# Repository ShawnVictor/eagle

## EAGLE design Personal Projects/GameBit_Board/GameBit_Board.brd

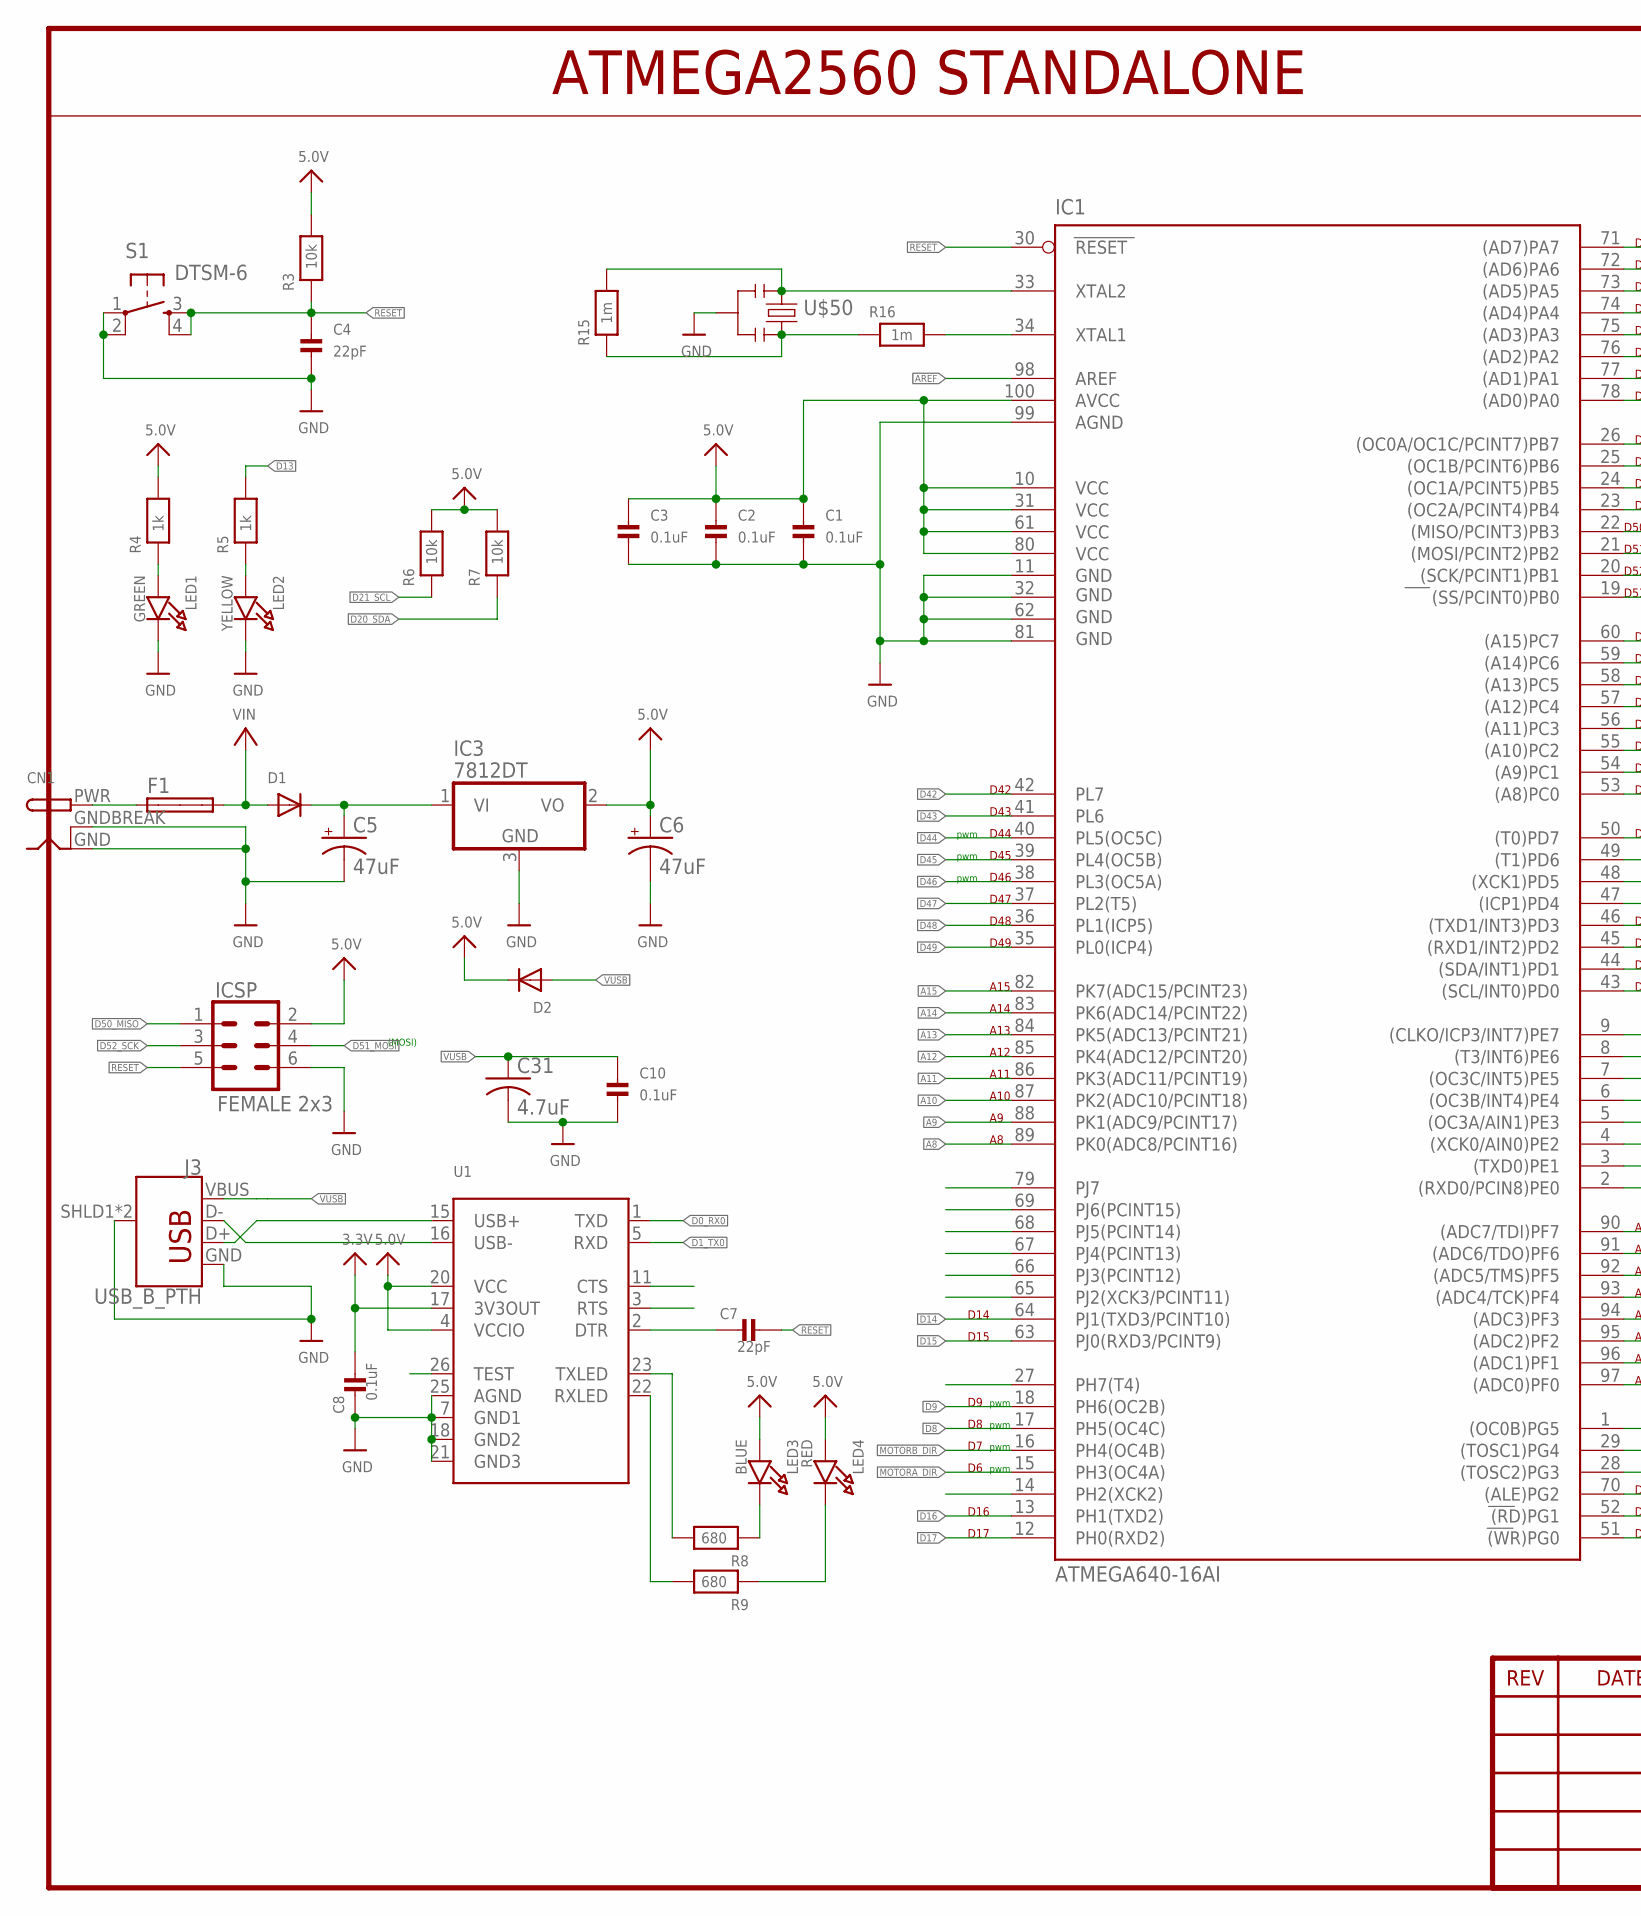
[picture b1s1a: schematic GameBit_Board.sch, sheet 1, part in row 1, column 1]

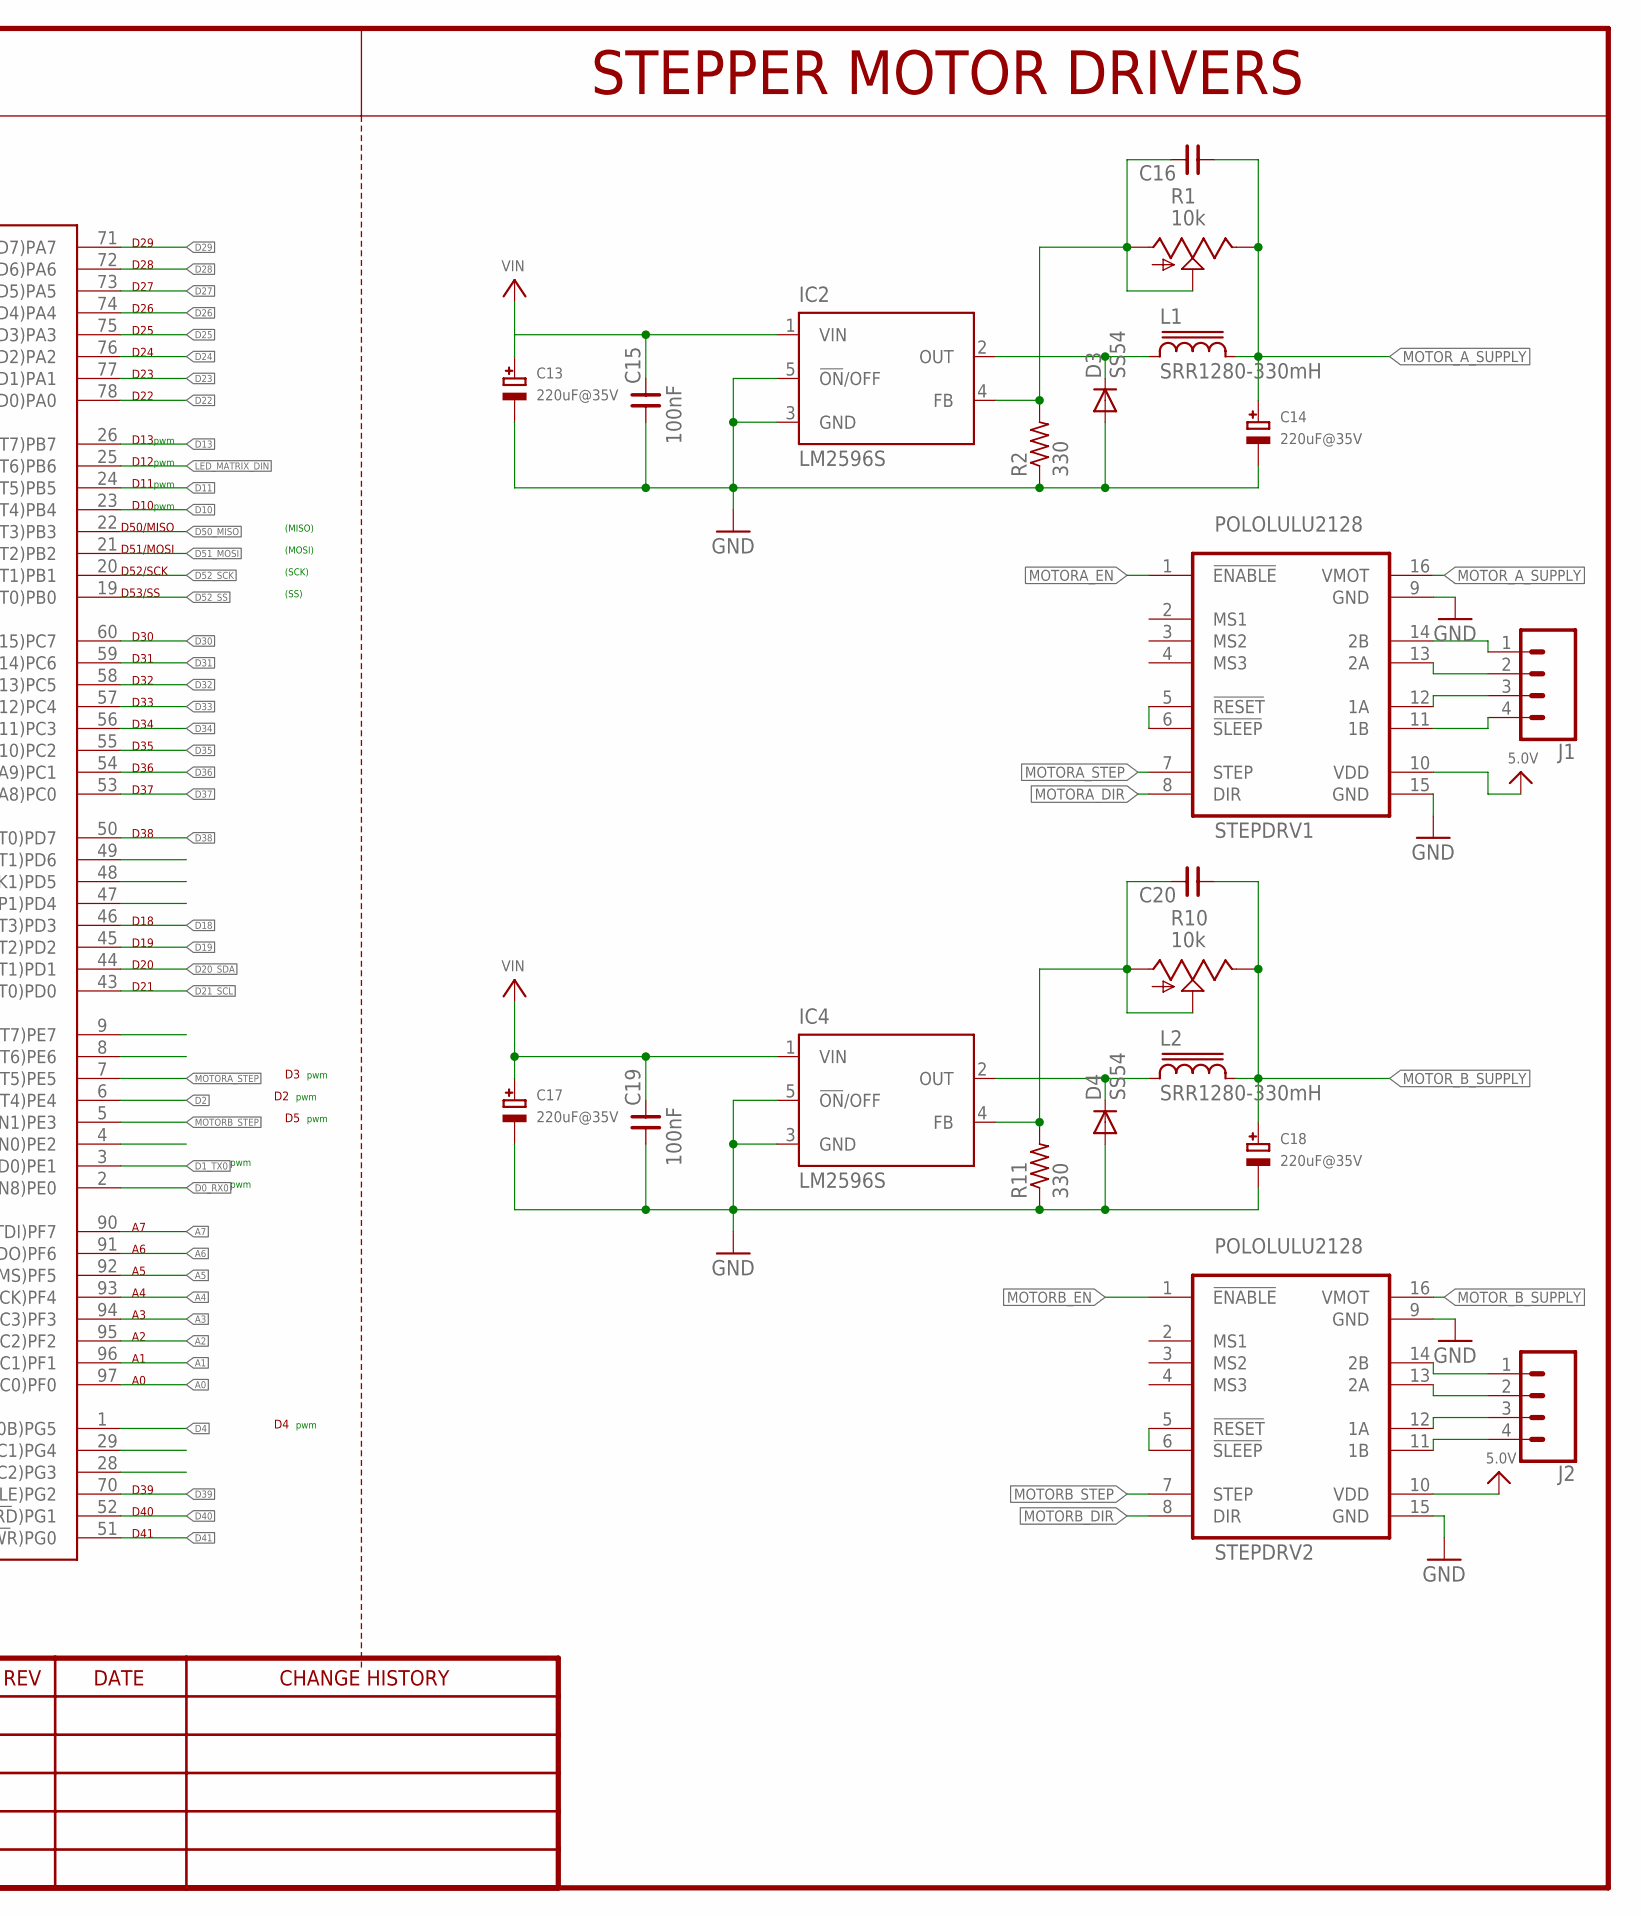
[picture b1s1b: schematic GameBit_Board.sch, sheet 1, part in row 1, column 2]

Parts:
C1, C2, C3, C8, C10: 0.1uF; 0603
C4, C7: 22pF; 0603
C5, C6: 47uF; PANASONIC_D
C13, C14, C17, C18: 220uF@35V; PANASONIC_D
C15, C19: 100nF; 0603
C16, C20: CNP-0603; 0603
C31: 4.7uF; C0805
CN1: DCBARRELPTH; DCJACK_2MM_PTH
D1, D2: DIODESOD-123; SOD-123
D3, D4: SS54; DO214AB
F1: SHK20L
IC1: ATMEGA640-16AI; TQFP100
IC2, IC4: LM2596S; TO263-5
IC3: 7812DT; TO252
ICSP: FEMALE 2x3; 2X3
J1, J2: CONN_04JST-PTH-VERT; JST-4-PTH-VERT
J3: USB_B_PTH; USB-B-PTH
L1, L2: SRR1280-330mH; SRR1280
LED1: GREEN; CHIPLED_0603
LED2: YELLOW; CHIPLED_0603
LED3: BLUE; CHIPLED_0603
LED4: RED; CHIPLED_0603
R1, R10: 10k; S64W
R2, R11: 330; R0603
R3, R6, R7: 10k; 0603
R4, R5: 1k; 0603
R8, R9: 680; 0603
R15, R16: 1m; 0805
S1: DTSM-6
STEPDRV1, STEPDRV2: POLOLULU2128
U1: FT232RLSSOP28; SSOP28DB
U$50: RESONATORSMD; RESONATOR-SMD

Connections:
3.3V: C8.2, U1.17 (3V3OUT)
5.0V: C1.1, C2.1, C3.1, C6.+, D2.C, IC1.10 (VCC), IC1.31 (VCC1), IC1.61 (VCC2), IC1.80 (VCC3), IC1.100 (AVCC), IC3.2 (VO), ICSP.2, LED3.A, LED4.A, R3.2, R4.2, R6.2, R7.2, STEPDRV1.10 (VDD), STEPDRV2.10 (VDD), U1.4 (VCCIO), U1.20 (VCC); also elsewhere on the board
A0: IC1.97 ((ADC0)PF0)
A1: IC1.96 ((ADC1)PF1)
A2: IC1.95 ((ADC2)PF2)
A3: IC1.94 ((ADC3)PF3)
A4: IC1.93 ((ADC4/TCK)PF4)
A5: IC1.92 ((ADC5/TMS)PF5)
A6: IC1.91 ((ADC6/TDO)PF6)
A7: IC1.90 ((ADC7/TDI)PF7)
A8: IC1.89 (PK0(ADC8/PCINT16))
A9: IC1.88 (PK1(ADC9/PCINT17))
A10: IC1.87 (PK2(ADC10/PCINT18))
A11: IC1.86 (PK3(ADC11/PCINT19))
A12: IC1.85 (PK4(ADC12/PCINT20))
A13: IC1.84 (PK5(ADC13/PCINT21))
A14: IC1.83 (PK6(ADC14/PCINT22))
A15: IC1.82 (PK7(ADC15/PCINT23))
AREF: IC1.98 (AREF)
D0_RX0: IC1.2 ((RXD0/PCIN8)PE0), U1.1 (TXD)
D1_TX0: IC1.3 ((TXD0)PE1), U1.5 (RXD)
D2: IC1.6 ((OC3B/INT4)PE4)
D4: IC1.1 ((OC0B)PG5)
D8: IC1.17 (PH5(OC4C))
D9: IC1.18 (PH6(OC2B))
D10: IC1.23 ((OC2A/PCINT4)PB4)
D11: IC1.24 ((OC1A/PCINT5)PB5)
D13: IC1.26 ((OC0A/OC1C/PCINT7)PB7), R5.2
D14: IC1.64 (PJ1(TXD3/PCINT10))
D15: IC1.63 (PJ0(RXD3/PCINT9))
D16: IC1.13 (PH1(TXD2))
D17: IC1.12 (PH0(RXD2))
D18: IC1.46 ((TXD1/INT3)PD3)
D19: IC1.45 ((RXD1/INT2)PD2)
D20_SDA: IC1.44 ((SDA/INT1)PD1), R7.1; also elsewhere on the board
D21_SCL: IC1.43 ((SCL/INT0)PD0), R6.1; also elsewhere on the board
D22: IC1.78 ((AD0)PA0)
D23: IC1.77 ((AD1)PA1)
D24: IC1.76 ((AD2)PA2)
D25: IC1.75 ((AD3)PA3)
D26: IC1.74 ((AD4)PA4)
D27: IC1.73 ((AD5)PA5)
D28: IC1.72 ((AD6)PA6)
D29: IC1.71 ((AD7)PA7)
D30: IC1.60 ((A15)PC7)
D31: IC1.59 ((A14)PC6)
D32: IC1.58 ((A13)PC5)
D33: IC1.57 ((A12)PC4)
D34: IC1.56 ((A11)PC3)
D35: IC1.55 ((A10)PC2)
D36: IC1.54 ((A9)PC1)
D37: IC1.53 ((A8)PC0)
D38: IC1.50 ((T0)PD7)
D39: IC1.70 ((ALE)PG2)
D40: IC1.52 ((RD)PG1)
D41: IC1.51 ((WR)PG0)
D42: IC1.42 (PL7)
D43: IC1.41 (PL6)
D44: IC1.40 (PL5(OC5C))
D45: IC1.39 (PL4(OC5B))
D46: IC1.38 (PL3(OC5A))
D47: IC1.37 (PL2(T5))
D48: IC1.36 (PL1(ICP5))
D49: IC1.35 (PL0(ICP4))
D50_MISO: IC1.22 ((MISO/PCINT3)PB3), ICSP.1
D51_MOSI: IC1.21 ((MOSI/PCINT2)PB2), ICSP.4
D52_SCK: IC1.20 ((SCK/PCINT1)PB1), ICSP.3
D52_SS: IC1.19 ((SS/PCINT0)PB0)
GND: C1.2, C2.2, C3.2, C4.2, C5.-, C6.-, C8.1, C10.1, C13.-, C14.-, C15.1, C17.-, C18.-, C19.1, C31.2, CN1.GND, CN1.GNDBREAK, D3.A, D4.A, IC1.11 (GND), IC1.32 (GND1), IC1.62 (GND2), IC1.81 (GND3), IC1.99 (AGND), IC2.3 (GND), IC2.5 (!ON!/OFF), IC3.3 (GND), IC4.3 (GND), IC4.5 (!ON!/OFF), ICSP.6, J3.GND, J3.SHLD1 (SHIELD), J3.SHLD2 (SHIELD), LED1.C, LED2.C, R2.1, R11.1, S1.1, S1.2, STEPDRV1.9 (GND), STEPDRV1.15 (GND), STEPDRV2.9 (GND), STEPDRV2.15 (GND), U1.7 (GND1), U1.18 (GND2), U1.21 (GND3), U1.25 (AGND), U$50.2; also elsewhere on the board
LED_MATRIX_DIN: IC1.25 ((OC1B/PCINT6)PB6); also elsewhere on the board
MOTORA_DIR: IC1.15 (PH3(OC4A)), STEPDRV1.8 (DIR)
MOTORA_EN: STEPDRV1.1 (!ENABLE)
MOTORA_STEP: IC1.7 ((OC3C/INT5)PE5), STEPDRV1.7 (STEP)
MOTORB_DIR: IC1.16 (PH4(OC4B)), STEPDRV2.8 (DIR)
MOTORB_EN: STEPDRV2.1 (!ENABLE)
MOTORB_STEP: IC1.5 ((OC3A/AIN1)PE3), STEPDRV2.7 (STEP)
MOTOR_A_SUPPLY: C14.+, C16.1, L1.2, R1.E, STEPDRV1.16 (VMOT)
MOTOR_B_SUPPLY: C18.+, C20.1, L2.2, R10.E, STEPDRV2.16 (VMOT)
unnamed: D3.C, IC2.2 (OUT), L1.1
unnamed: CN1.PWR, F1.1A
unnamed: J3.D+, U1.15 (USB+)
unnamed: J3.D-, U1.16 (USB-)
unnamed: LED1.A, R4.1
unnamed: LED2.A, R5.1
unnamed: LED3.C, R8.1
unnamed: R9.2, U1.22 (RXLED)
unnamed: R8.2, U1.23 (TXLED)
unnamed: LED4.C, R9.1
unnamed: C16.2, IC2.4 (FB), R1.A, R1.S, R2.2
unnamed: C7.1, U1.2 (DTR)
unnamed: D4.C, IC4.2 (OUT), L2.1
unnamed: C20.2, IC4.4 (FB), R10.A, R10.S, R11.2
unnamed: J1.1, STEPDRV1.14 (2B)
unnamed: J1.2, STEPDRV1.13 (2A)
unnamed: J1.3, STEPDRV1.12 (1A)
unnamed: J1.4, STEPDRV1.11 (1B)
unnamed: J2.1, STEPDRV2.14 (2B)
unnamed: J2.2, STEPDRV2.13 (2A)
unnamed: J2.3, STEPDRV2.12 (1A)
unnamed: J2.4, STEPDRV2.11 (1B)
unnamed: STEPDRV1.5 (!RESET), STEPDRV1.6 (!SLEEP)
unnamed: STEPDRV2.5 (!RESET), STEPDRV2.6 (!SLEEP)
unnamed: R15.1, R16.1, U$50.3
unnamed: IC1.34 (XTAL1), R16.2
unnamed: C5.+, D1.C, IC3.1 (VI)
RESET: C4.1, C7.2, IC1.30 (RESET), ICSP.5, R3.1, S1.3, S1.4
VIN: C13.+, C15.2, C17.+, C19.2, D1.A, F1.2A, IC2.1 (VIN), IC4.1 (VIN); also elsewhere on the board
VUSB: C10.2, C31.1, D2.A, J3.VBUS
XTAL2: IC1.33 (XTAL2), R15.2, U$50.1

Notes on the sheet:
pwm
(SS)
(SCK)
(MOSI)
(MISO)
ATMEGA2560 STANDALONE
STEPPER MOTOR DRIVERS
D10
D11
D12
D13
D14
D15
D16
D17
D46
D45
D44
D43
D42
D47
D48
D49
D18
D19
D20
D21
D22
D23
D24
D25
D26
D27
D28
D29
D30
D31
D32
D33
D34

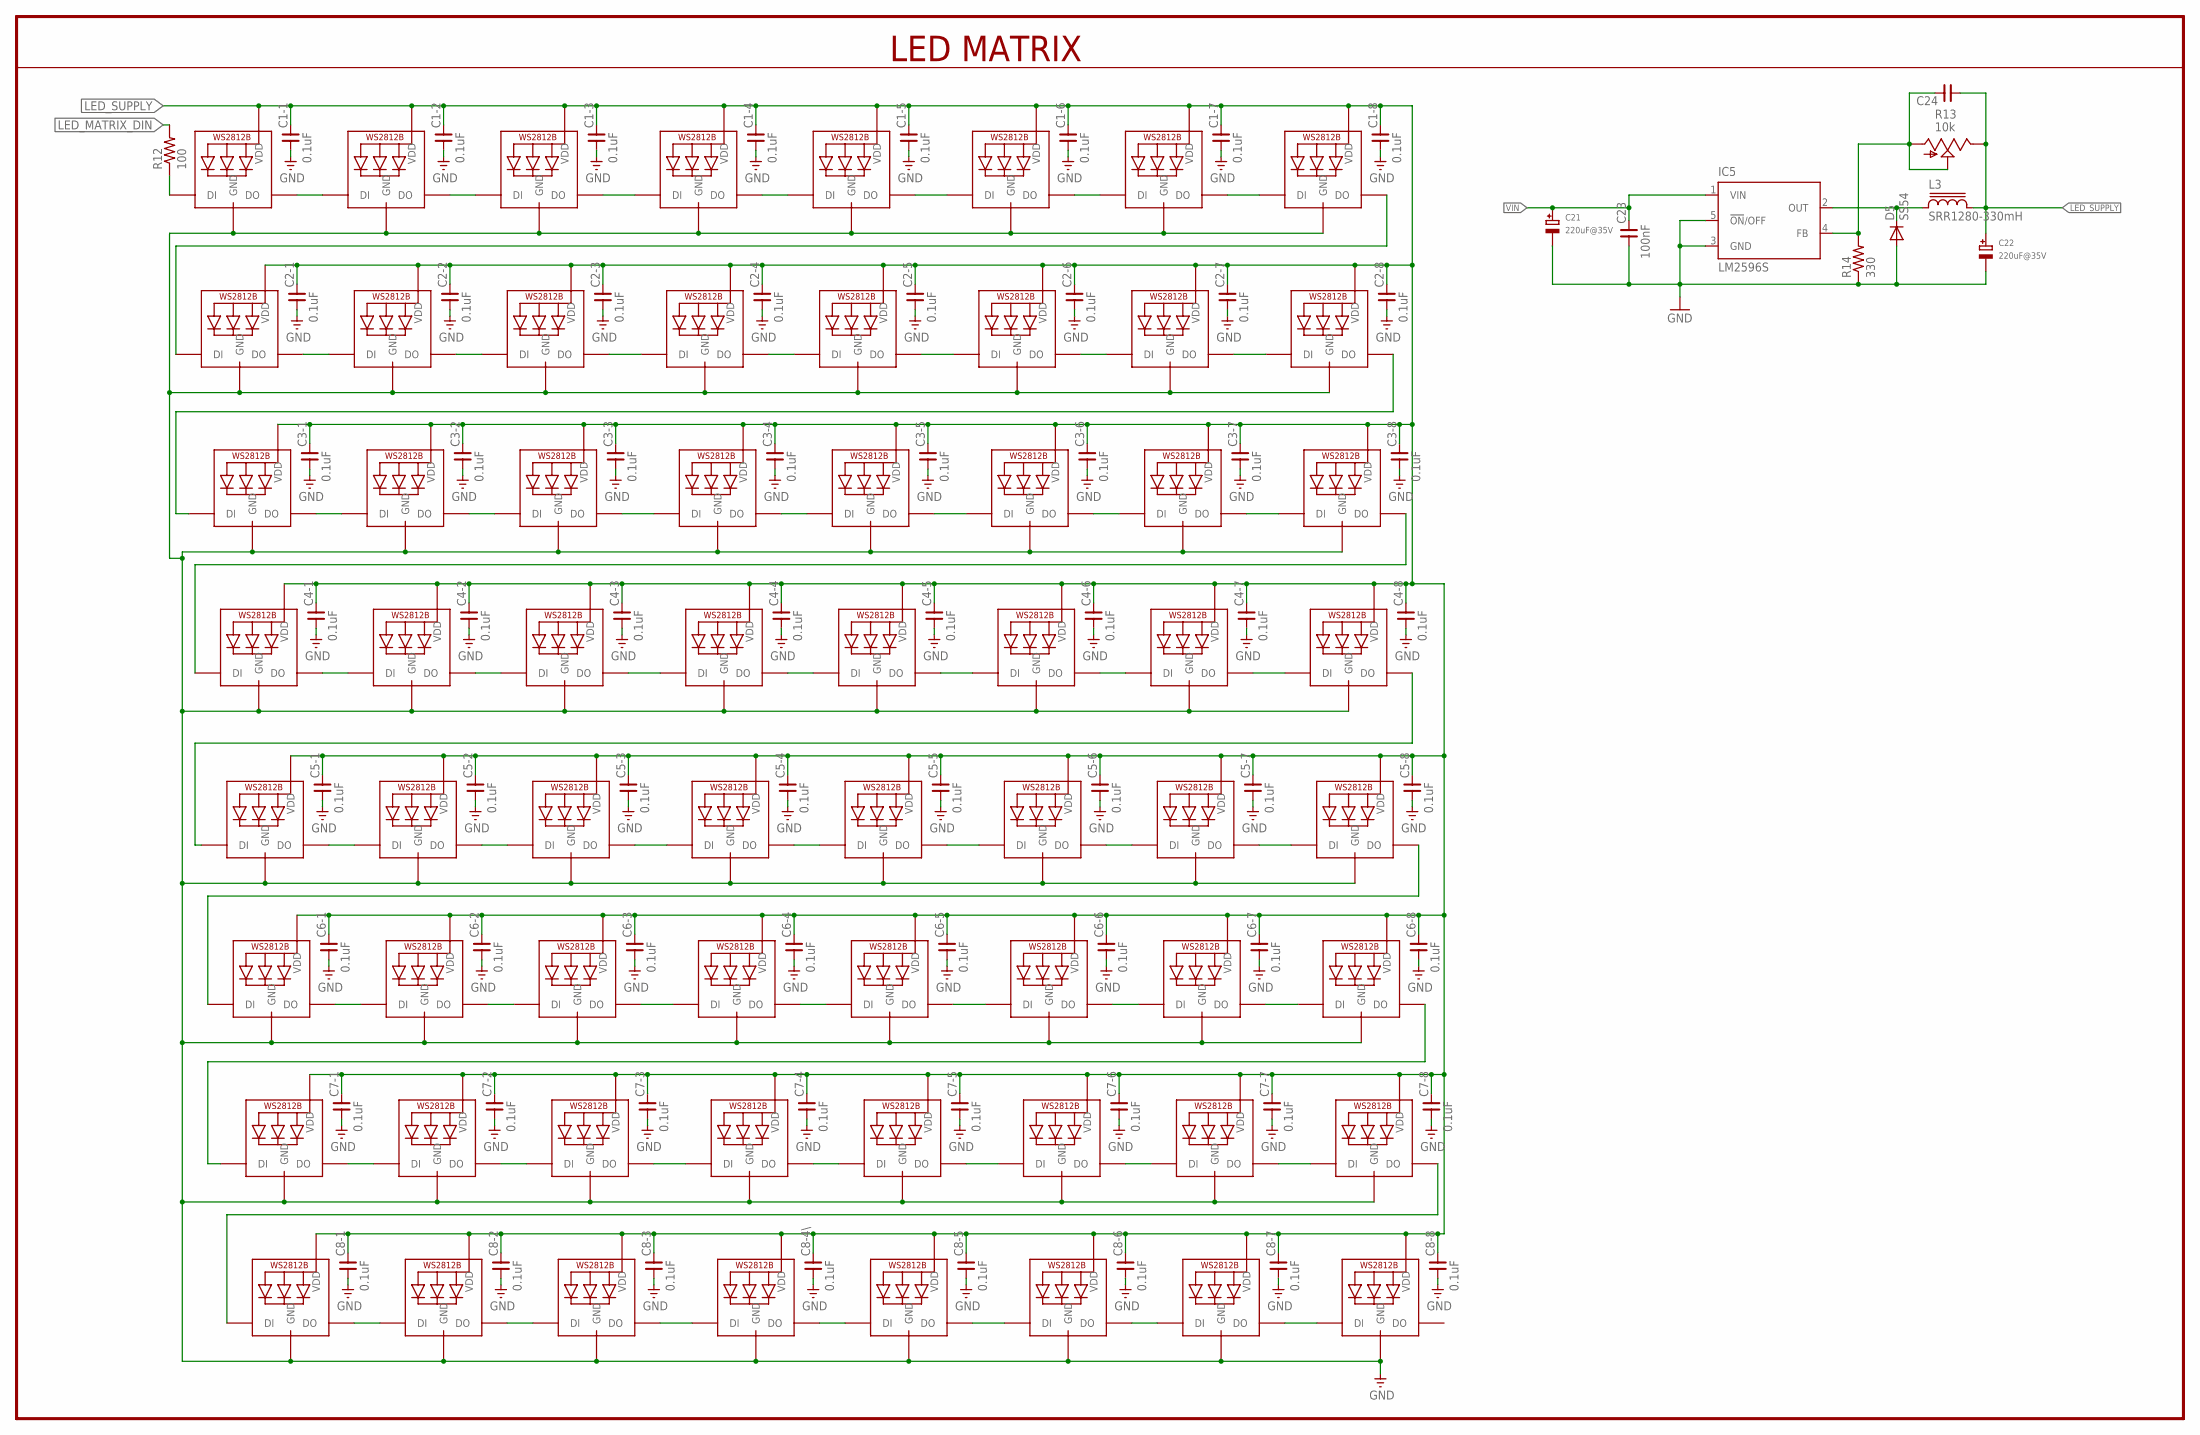
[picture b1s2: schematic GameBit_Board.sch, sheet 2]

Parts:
C1-1, C1-2, C1-3, C1-4, C1-5, C1-6, C1-7, C1-8, C2-1, C2-2, C2-3, C2-4, C2-5, C2-6, C2-7, C2-8, C3-1, C3-2, C3-3, C3-4, C3-5, C3-6, C3-7, C3-8, C4-1, C4-2, C4-3, C4-4, C4-5, C4-6, C4-7, C4-8, C5-1, C5-2, C5-3, C5-4, C5-5, C5-6, C5-7, C5-8, C6-1, C6-2, C6-3, C6-4, C6-5, C6-6, C6-7, C6-8, C7-1, C7-2, C7-3, C7-4, C7-5, C7-6, C7-7, C7-8, C8-1, C8-2, C8-3, C8-4\, C8-5, C8-6, C8-7, C8-8: 0.1uF; 0805
C21, C22: 220uF@35V; PANASONIC_D
C23: 100nF; 0603
C24: CNP-0603; 0603
D5: SS54; DO214AB
IC5: LM2596S; TO263-5
L3: SRR1280-330mH; SRR1280
LED1-1, LED1-2, LED1-3, LED1-4, LED1-5, LED1-6, LED1-7, LED1-8, LED2-1, LED2-2, LED2-3, LED2-4, LED2-5, LED2-6, LED2-7, LED2-8, LED3-1, LED3-2, LED3-3, LED3-4, LED3-5, LED3-6, LED3-7, LED3-8, LED4-1, LED4-2, LED4-3, LED4-4, LED4-5, LED4-6, LED4-7, LED4-8, LED5-1, LED5-2, LED5-3, LED5-4, LED5-5, LED5-6, LED5-7, LED5-8, LED6-1, LED6-2, LED6-3, LED6-4, LED6-5, LED6-6, LED6-7, LED6-8, LED7-1, LED7-2, LED7-3, LED7-4, LED7-5, LED7-6, LED7-7, LED7-8, LED8-1, LED8-2, LED8-3, LED8-4, LED8-5, LED8-6, LED8-7, LED8-8: WS2812B5050; WS2812B
R12: 100; R0805
R13: 10k; S64W
R14: 330; R0603

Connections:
GND: C1-1.1, C1-2.1, C1-3.1, C1-4.1, C1-5.1, C1-6.1, C1-7.1, C1-8.1, C2-1.1, C2-2.1, C2-3.1, C2-4.1, C2-5.1, C2-6.1, C2-7.1, C2-8.1, C3-1.1, C3-2.1, C3-3.1, C3-4.1, C3-5.1, C3-6.1, C3-7.1, C3-8.1, C4-1.1, C4-2.1, C4-3.1, C4-4.1, C4-5.1, C4-6.1, C4-7.1, C4-8.1, C5-1.1, C5-2.1, C5-3.1, C5-4.1, C5-5.1, C5-6.1, C5-7.1, C5-8.1, C6-1.1, C6-2.1, C6-3.1, C6-4.1, C6-5.1, C6-6.1, C6-7.1, C6-8.1, C7-1.1, C7-2.1, C7-3.1, C7-4.1, C7-5.1, C7-6.1, C7-7.1, C7-8.1, C8-1.1, C8-2.1, C8-3.1, C8-4\.1, C8-5.1, C8-6.1, C8-7.1, C8-8.1, C21.-, C22.-, C23.1, D5.A, IC5.3 (GND), IC5.5 (!ON!/OFF), LED1-1.3-GND (GND), LED1-2.3-GND (GND), LED1-3.3-GND (GND), LED1-4.3-GND (GND), LED1-5.3-GND (GND), LED1-6.3-GND (GND), LED1-7.3-GND (GND), LED1-8.3-GND (GND), LED2-1.3-GND (GND), LED2-2.3-GND (GND), LED2-3.3-GND (GND), LED2-4.3-GND (GND), LED2-5.3-GND (GND), LED2-6.3-GND (GND), LED2-7.3-GND (GND), LED2-8.3-GND (GND), LED3-1.3-GND (GND), LED3-2.3-GND (GND), LED3-3.3-GND (GND), LED3-4.3-GND (GND), LED3-5.3-GND (GND), LED3-6.3-GND (GND), LED3-7.3-GND (GND), LED3-8.3-GND (GND), LED4-1.3-GND (GND), LED4-2.3-GND (GND), LED4-3.3-GND (GND), LED4-4.3-GND (GND), LED4-5.3-GND (GND), LED4-6.3-GND (GND), LED4-7.3-GND (GND), LED4-8.3-GND (GND), LED5-1.3-GND (GND), LED5-2.3-GND (GND), LED5-3.3-GND (GND), LED5-4.3-GND (GND), LED5-5.3-GND (GND), LED5-6.3-GND (GND), LED5-7.3-GND (GND), LED5-8.3-GND (GND), LED6-1.3-GND (GND), LED6-2.3-GND (GND), LED6-3.3-GND (GND), LED6-4.3-GND (GND), LED6-5.3-GND (GND), LED6-6.3-GND (GND), LED6-7.3-GND (GND), LED6-8.3-GND (GND), LED7-1.3-GND (GND), LED7-2.3-GND (GND), LED7-3.3-GND (GND), LED7-4.3-GND (GND), LED7-5.3-GND (GND), LED7-6.3-GND (GND), LED7-7.3-GND (GND), LED7-8.3-GND (GND), LED8-1.3-GND (GND), LED8-2.3-GND (GND), LED8-3.3-GND (GND), LED8-4.3-GND (GND), LED8-5.3-GND (GND), LED8-6.3-GND (GND), LED8-7.3-GND (GND), LED8-8.3-GND (GND), R14.1; also elsewhere on the board
LED_MATRIX_DIN: R12.2; also elsewhere on the board
LED_SUPPLY: C1-1.2, C1-2.2, C1-3.2, C1-4.2, C1-5.2, C1-6.2, C1-7.2, C1-8.2, C2-1.2, C2-2.2, C2-3.2, C2-4.2, C2-5.2, C2-6.2, C2-7.2, C2-8.2, C3-1.2, C3-2.2, C3-3.2, C3-4.2, C3-5.2, C3-6.2, C3-7.2, C3-8.2, C4-1.2, C4-2.2, C4-3.2, C4-4.2, C4-5.2, C4-6.2, C4-7.2, C4-8.2, C5-1.2, C5-2.2, C5-3.2, C5-4.2, C5-5.2, C5-6.2, C5-7.2, C5-8.2, C6-1.2, C6-2.2, C6-3.2, C6-4.2, C6-5.2, C6-6.2, C6-7.2, C6-8.2, C7-1.2, C7-2.2, C7-3.2, C7-4.2, C7-5.2, C7-6.2, C7-7.2, C7-8.2, C8-1.2, C8-2.2, C8-3.2, C8-4\.2, C8-5.2, C8-6.2, C8-7.2, C8-8.2, C22.+, C24.1, L3.2, LED1-1.1-VDD (VDD), LED1-2.1-VDD (VDD), LED1-3.1-VDD (VDD), LED1-4.1-VDD (VDD), LED1-5.1-VDD (VDD), LED1-6.1-VDD (VDD), LED1-7.1-VDD (VDD), LED1-8.1-VDD (VDD), LED2-1.1-VDD (VDD), LED2-2.1-VDD (VDD), LED2-3.1-VDD (VDD), LED2-4.1-VDD (VDD), LED2-5.1-VDD (VDD), LED2-6.1-VDD (VDD), LED2-7.1-VDD (VDD), LED2-8.1-VDD (VDD), LED3-1.1-VDD (VDD), LED3-2.1-VDD (VDD), LED3-3.1-VDD (VDD), LED3-4.1-VDD (VDD), LED3-5.1-VDD (VDD), LED3-6.1-VDD (VDD), LED3-7.1-VDD (VDD), LED3-8.1-VDD (VDD), LED4-1.1-VDD (VDD), LED4-2.1-VDD (VDD), LED4-3.1-VDD (VDD), LED4-4.1-VDD (VDD), LED4-5.1-VDD (VDD), LED4-6.1-VDD (VDD), LED4-7.1-VDD (VDD), LED4-8.1-VDD (VDD), LED5-1.1-VDD (VDD), LED5-2.1-VDD (VDD), LED5-3.1-VDD (VDD), LED5-4.1-VDD (VDD), LED5-5.1-VDD (VDD), LED5-6.1-VDD (VDD), LED5-7.1-VDD (VDD), LED5-8.1-VDD (VDD), LED6-1.1-VDD (VDD), LED6-2.1-VDD (VDD), LED6-3.1-VDD (VDD), LED6-4.1-VDD (VDD), LED6-5.1-VDD (VDD), LED6-6.1-VDD (VDD), LED6-7.1-VDD (VDD), LED6-8.1-VDD (VDD), LED7-1.1-VDD (VDD), LED7-2.1-VDD (VDD), LED7-3.1-VDD (VDD), LED7-4.1-VDD (VDD), LED7-5.1-VDD (VDD), LED7-6.1-VDD (VDD), LED7-7.1-VDD (VDD), LED7-8.1-VDD (VDD), LED8-1.1-VDD (VDD), LED8-2.1-VDD (VDD), LED8-3.1-VDD (VDD), LED8-4.1-VDD (VDD), LED8-5.1-VDD (VDD), LED8-6.1-VDD (VDD), LED8-7.1-VDD (VDD), LED8-8.1-VDD (VDD), R13.E
LED_SUPPLY1: LED1-8.2-DOUT (DO), LED2-1.4-DIN (DI)
LED_SUPPLY3: LED3-8.2-DOUT (DO), LED4-1.4-DIN (DI)
LED_SUPPLY4: LED5-8.2-DOUT (DO), LED6-1.4-DIN (DI)
LED_SUPPLY5: LED7-8.2-DOUT (DO), LED8-1.4-DIN (DI)
unnamed: LED1-1.4-DIN (DI), R12.1
unnamed: LED1-1.2-DOUT (DO), LED1-2.4-DIN (DI)
unnamed: LED1-2.2-DOUT (DO), LED1-3.4-DIN (DI)
unnamed: LED1-3.2-DOUT (DO), LED1-4.4-DIN (DI)
unnamed: LED1-4.2-DOUT (DO), LED1-5.4-DIN (DI)
unnamed: LED1-5.2-DOUT (DO), LED1-6.4-DIN (DI)
unnamed: LED1-6.2-DOUT (DO), LED1-7.4-DIN (DI)
unnamed: LED1-7.2-DOUT (DO), LED1-8.4-DIN (DI)
unnamed: D5.C, IC5.2 (OUT), L3.1
unnamed: LED2-1.2-DOUT (DO), LED2-2.4-DIN (DI)
unnamed: LED2-2.2-DOUT (DO), LED2-3.4-DIN (DI)
unnamed: LED2-3.2-DOUT (DO), LED2-4.4-DIN (DI)
unnamed: LED2-4.2-DOUT (DO), LED2-5.4-DIN (DI)
unnamed: LED2-5.2-DOUT (DO), LED2-6.4-DIN (DI)
unnamed: LED2-6.2-DOUT (DO), LED2-7.4-DIN (DI)
unnamed: LED2-7.2-DOUT (DO), LED2-8.4-DIN (DI)
unnamed: C24.2, IC5.4 (FB), R13.A, R13.S, R14.2
unnamed: LED5-1.2-DOUT (DO), LED5-2.4-DIN (DI)
unnamed: LED3-1.2-DOUT (DO), LED3-2.4-DIN (DI)
unnamed: LED3-2.2-DOUT (DO), LED3-3.4-DIN (DI)
unnamed: LED3-3.2-DOUT (DO), LED3-4.4-DIN (DI)
unnamed: LED3-4.2-DOUT (DO), LED3-5.4-DIN (DI)
unnamed: LED3-5.2-DOUT (DO), LED3-6.4-DIN (DI)
unnamed: LED3-6.2-DOUT (DO), LED3-7.4-DIN (DI)
unnamed: LED3-7.2-DOUT (DO), LED3-8.4-DIN (DI)
unnamed: LED6-6.2-DOUT (DO), LED6-7.4-DIN (DI)
unnamed: LED4-1.2-DOUT (DO), LED4-2.4-DIN (DI)
unnamed: LED4-2.2-DOUT (DO), LED4-3.4-DIN (DI)
unnamed: LED4-3.2-DOUT (DO), LED4-4.4-DIN (DI)
unnamed: LED4-4.2-DOUT (DO), LED4-5.4-DIN (DI)
unnamed: LED4-5.2-DOUT (DO), LED4-6.4-DIN (DI)
unnamed: LED4-6.2-DOUT (DO), LED4-7.4-DIN (DI)
unnamed: LED4-7.2-DOUT (DO), LED4-8.4-DIN (DI)
unnamed: LED5-2.2-DOUT (DO), LED5-3.4-DIN (DI)
unnamed: LED2-8.2-DOUT (DO), LED3-1.4-DIN (DI)
unnamed: LED5-3.2-DOUT (DO), LED5-4.4-DIN (DI)
unnamed: LED5-4.2-DOUT (DO), LED5-5.4-DIN (DI)
unnamed: LED5-5.2-DOUT (DO), LED5-6.4-DIN (DI)
unnamed: LED5-6.2-DOUT (DO), LED5-7.4-DIN (DI)
unnamed: LED5-7.2-DOUT (DO), LED5-8.4-DIN (DI)
unnamed: LED6-1.2-DOUT (DO), LED6-2.4-DIN (DI)
unnamed: LED6-2.2-DOUT (DO), LED6-3.4-DIN (DI)
unnamed: LED6-3.2-DOUT (DO), LED6-4.4-DIN (DI)
unnamed: LED6-4.2-DOUT (DO), LED6-5.4-DIN (DI)
unnamed: LED6-5.2-DOUT (DO), LED6-6.4-DIN (DI)
unnamed: LED6-7.2-DOUT (DO), LED6-8.4-DIN (DI)
unnamed: LED7-1.2-DOUT (DO), LED7-2.4-DIN (DI)
unnamed: LED7-2.2-DOUT (DO), LED7-3.4-DIN (DI)
unnamed: LED7-3.2-DOUT (DO), LED7-4.4-DIN (DI)
unnamed: LED7-4.2-DOUT (DO), LED7-5.4-DIN (DI)
unnamed: LED7-5.2-DOUT (DO), LED7-6.4-DIN (DI)
unnamed: LED7-6.2-DOUT (DO), LED7-7.4-DIN (DI)
unnamed: LED7-7.2-DOUT (DO), LED7-8.4-DIN (DI)
unnamed: LED8-1.2-DOUT (DO), LED8-2.4-DIN (DI)
unnamed: LED8-2.2-DOUT (DO), LED8-3.4-DIN (DI)
unnamed: LED8-3.2-DOUT (DO), LED8-4.4-DIN (DI)
unnamed: LED8-4.2-DOUT (DO), LED8-5.4-DIN (DI)
unnamed: LED8-5.2-DOUT (DO), LED8-6.4-DIN (DI)
unnamed: LED8-6.2-DOUT (DO), LED8-7.4-DIN (DI)
unnamed: LED8-7.2-DOUT (DO), LED8-8.4-DIN (DI)
unnamed: LED6-8.2-DOUT (DO), LED7-1.4-DIN (DI)
unnamed: LED4-8.2-DOUT (DO), LED5-1.4-DIN (DI)
VIN: C21.+, C23.2, IC5.1 (VIN); also elsewhere on the board

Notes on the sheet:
LED MATRIX

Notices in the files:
parts and their libraries:
SparkFun-Connectors: Licensing: Creative Commons ShareAlike 4.0 International - https://creativecommons.org/licenses/by-sa/4.0
inductor-bourns: Copyright (C) 2008, Bob Starr
dframes: Copyright (C) 2004, Bob Starr (bobstarr@mindspring.com)
supply0: Copyright (C) 2007, Bob Starr
